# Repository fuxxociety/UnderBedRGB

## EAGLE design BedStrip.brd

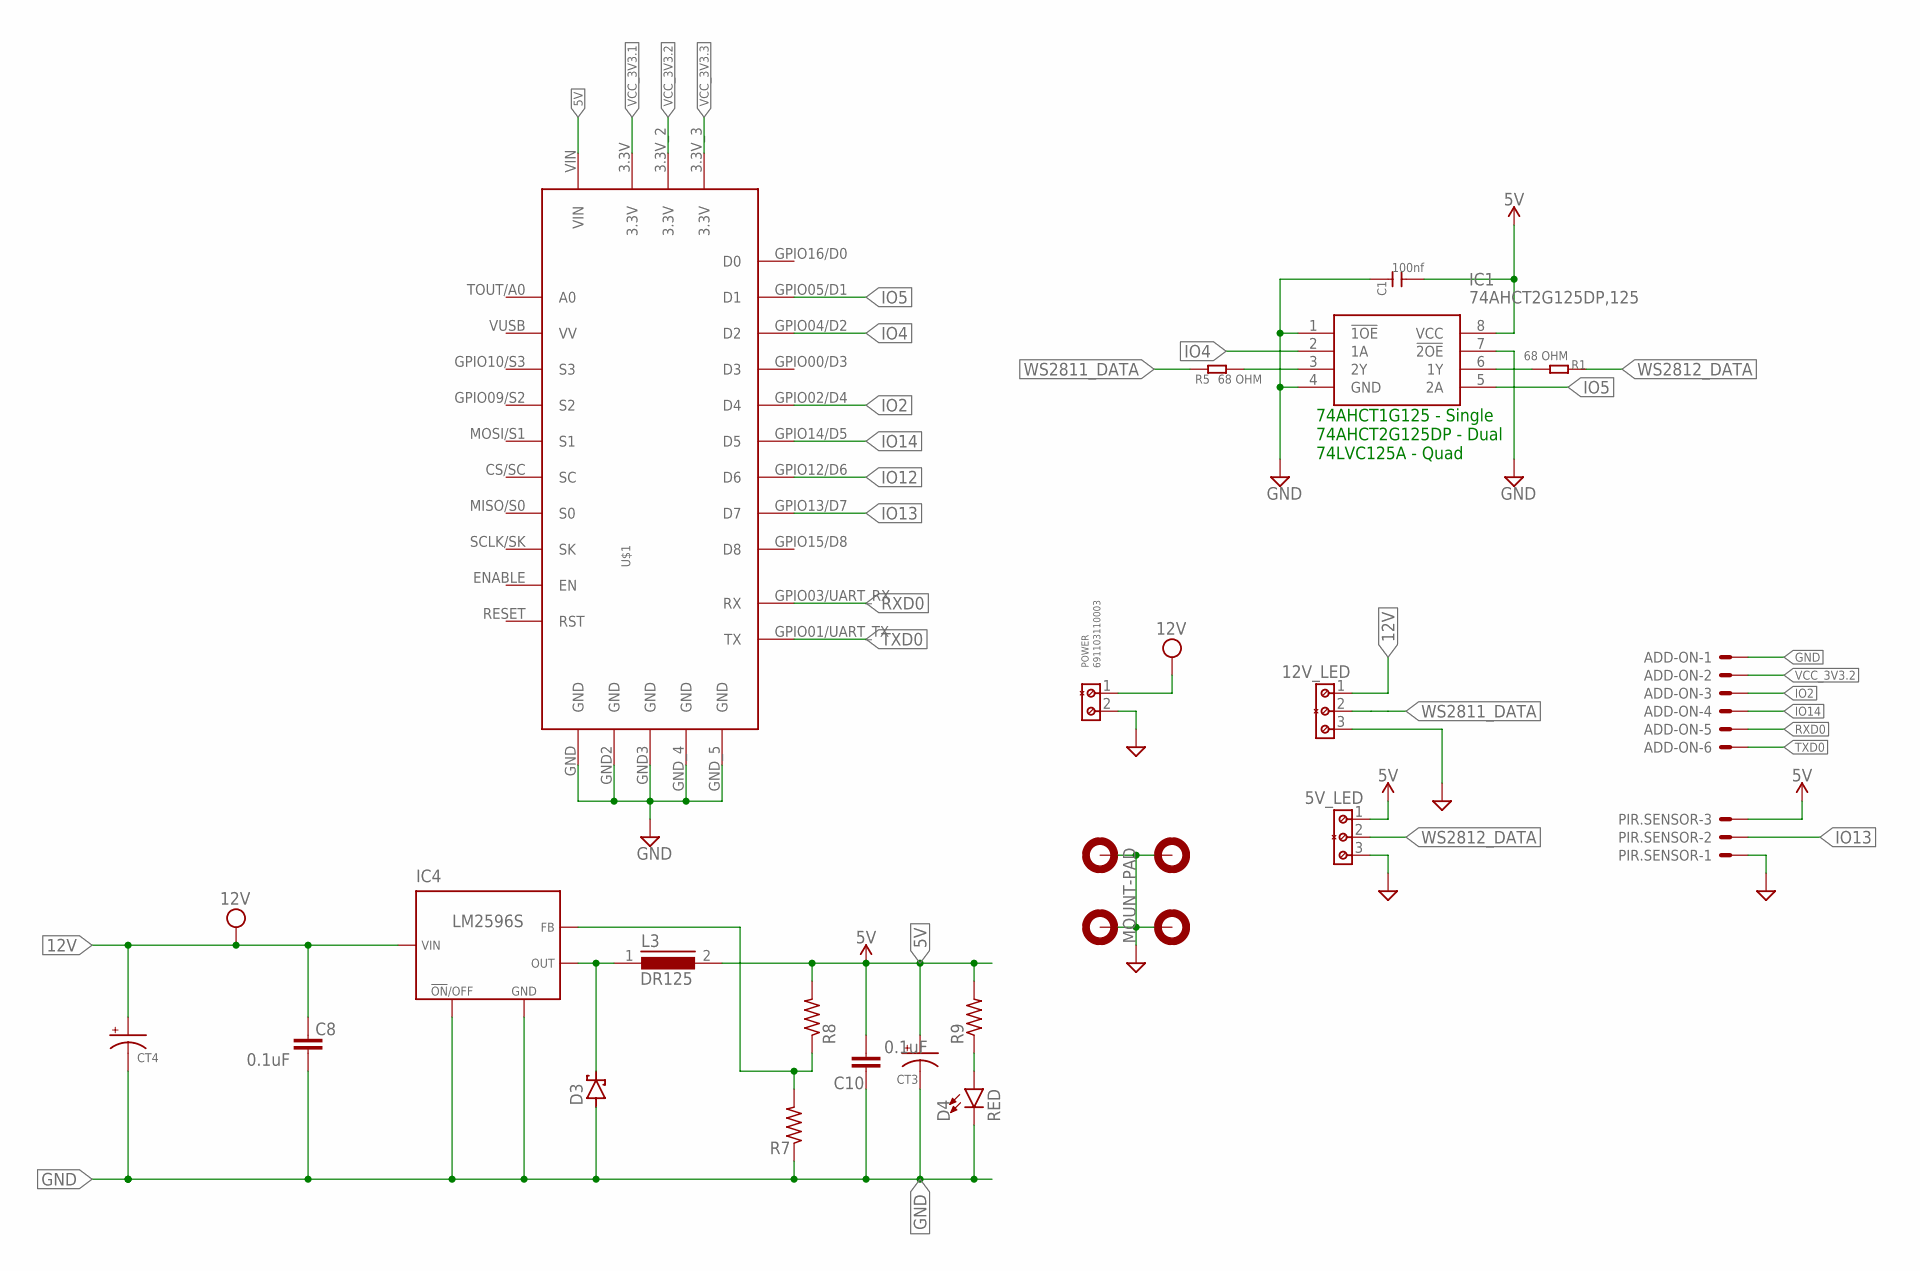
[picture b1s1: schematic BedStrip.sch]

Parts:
5V_LED, 12V_LED: 691103110003; WR-TB_3.50-3.81_3POS
ADD-ON: JST-XH-06-PIN-VERT-ROUND-PAD; JST-XH-06-VERT-ROUND-PAD
C1: 100nf; C0603
C8, C10: 0.1uF; CAPC1608X85
CT3, CT4: 220UF; CAPAE830X1050N
D3: SCHOTTKY-DIODESMD; SMB
D4: RED; LED-0603
H1, H2, H4: MOUNT-PAD-ROUND3.2; 3,2-PAD
H3: MOUNT-PAD; 3,2-PAD
IC1: 74AHCT2G125DP,125; SOP65P400X110-8N
IC4: LM2596S; TO263-5
L3: DR125
PIR.SENSOR: JST-XH-03-PIN-VERT-ROUND-PAD; JST-XH-03-VERT-ROUND-PAD
POWER: 691103110003; WR-TB_3.50-3.81_2POS
R1, R5: 68 OHM; R0603
R7, R8, R9: R-US_R0603; R0603
U$1: DEVBOARD_ESP8266_NODEMCU_V3DEVBOARD; DEVBOARD_ESP8266_NODEMCU_V3

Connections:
5V: 5V_LED.1, C1.2, C10.1, CT3.1 (+), IC1.8 (VCC), L3.2, PIR.SENSOR.3, R8.2, R9.2, U$1.VIN
12V: 12V_LED.1, C8.2, CT4.1 (+), IC4.1 (VIN), POWER.1
GND: 5V_LED.3, 12V_LED.3, ADD-ON.1, C1.1, C8.1, C10.2, CT3.2 (-), CT4.2 (-), D3.A, D4.C, H1.B3,2, H2.B3,2, H3.B3,2, H4.B3,2, IC1.1 (!1OE), IC1.4 (GND), IC1.7 (!2OE), IC4.3 (GND), IC4.5 (!ON!/OFF), IC4.6 (GND), PIR.SENSOR.1, POWER.2, R7.1, U$1.GND, U$1.GND2 (GND), U$1.GND3 (GND), U$1.GND_4 (GND), U$1.GND_5 (GND)
IO2: ADD-ON.3, U$1.GPIO02/D4 (D4)
IO4: IC1.2 (1A), U$1.GPIO04/D2 (D2)
IO5: IC1.5 (2A), U$1.GPIO05/D1 (D1)
IO12: U$1.GPIO12/D6 (D6)
IO13: PIR.SENSOR.2, U$1.GPIO13/D7 (D7)
IO14: ADD-ON.4, U$1.GPIO14/D5 (D5)
unnamed: IC1.6 (1Y), R1.2
unnamed: D3.C, IC4.2 (OUT), L3.1
unnamed: D4.A, R9.1
unnamed: IC4.4 (FB), R7.2, R8.1
unnamed: IC1.3 (2Y), R5.2
RXD0: ADD-ON.5, U$1.GPIO03/UART_RX (RX)
TXD0: ADD-ON.6, U$1.GPIO01/UART_TX (TX)
VCC_3V3.1: U$1.3.3V
VCC_3V3.2: ADD-ON.2, U$1.3.3V_2 (3.3V)
VCC_3V3.3: U$1.3.3V_3 (3.3V)
WS2811_DATA: 12V_LED.2, R5.1
WS2812_DATA: 5V_LED.2, R1.1

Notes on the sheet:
74AHCT1G125 - Single 74AHCT2G125DP - Dual 74LVC125A - Quad

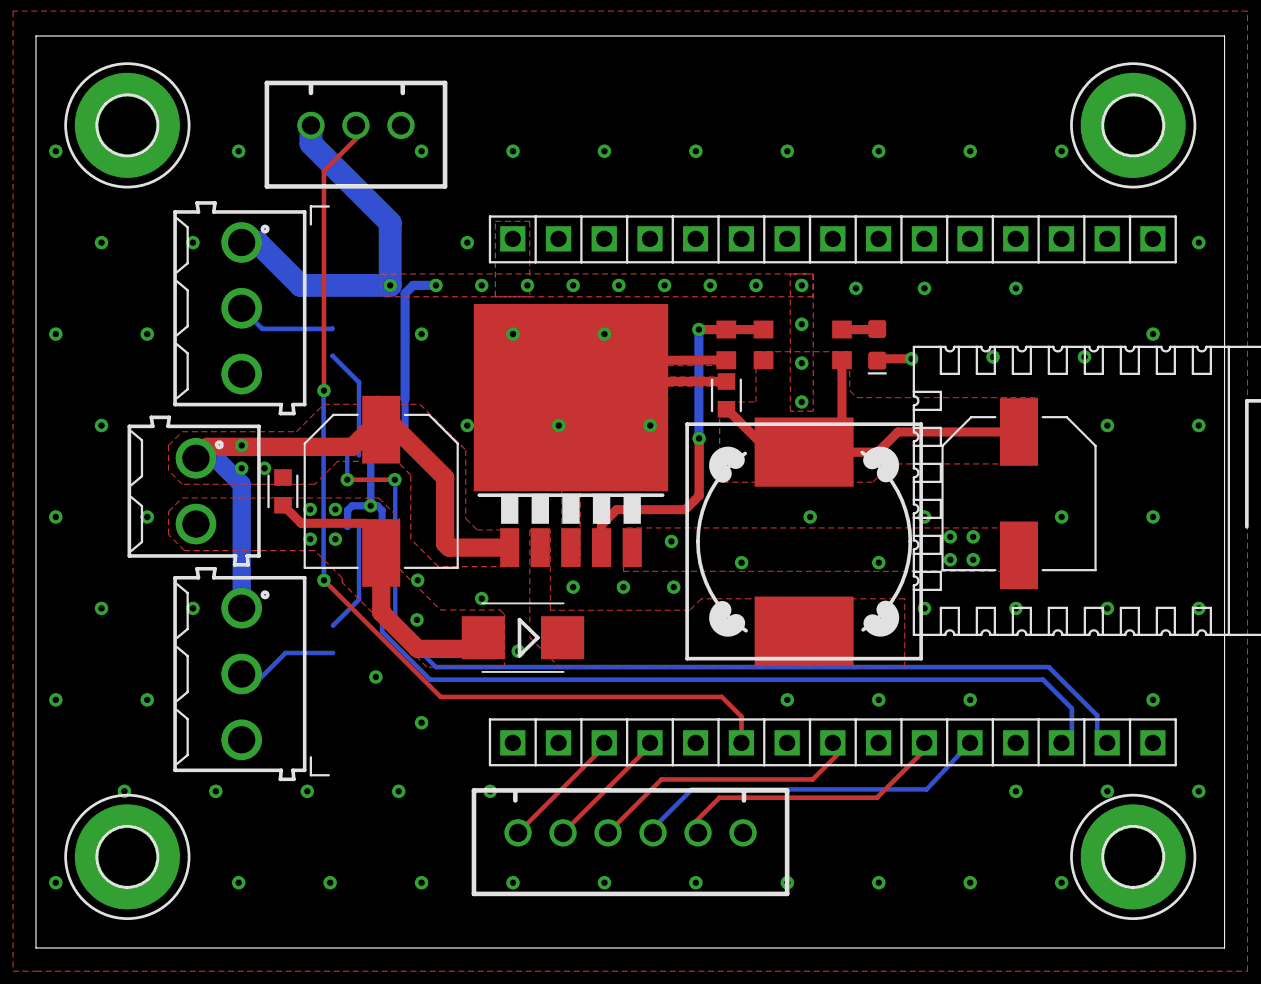
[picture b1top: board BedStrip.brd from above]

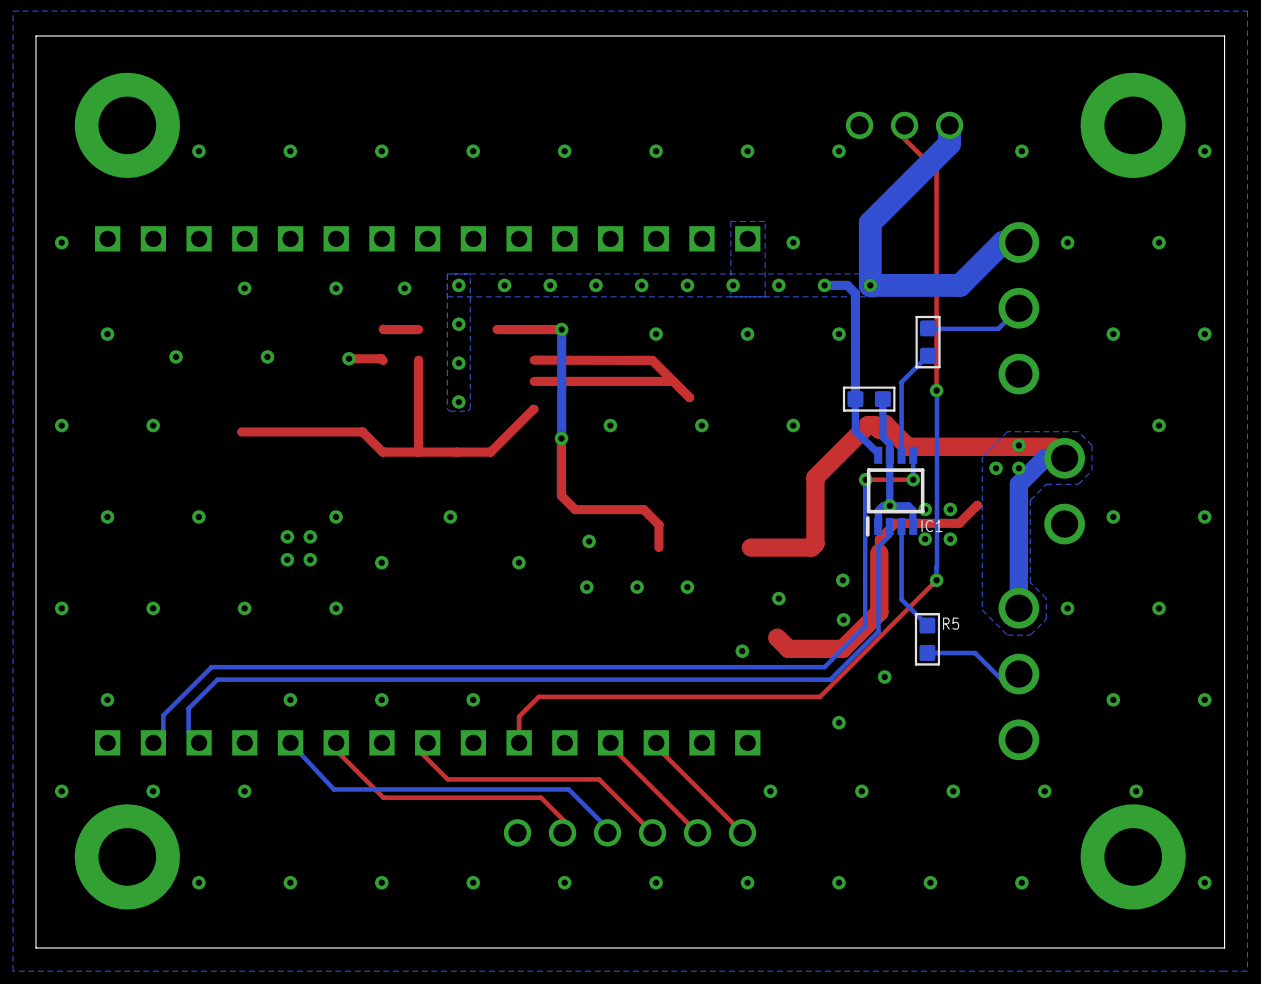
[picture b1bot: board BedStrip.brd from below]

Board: 2 copper layers, 66.0 x 50.7 mm, 25 parts (4 on the bottom side), 18 nets.

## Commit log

2022-09-15 Ready for PCB MFG

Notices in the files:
parts and their libraries:
SparkFun-LED: Licensing: Creative Commons ShareAlike 4.0 International - https://creativecommons.org/licenses/by-sa/4.0
